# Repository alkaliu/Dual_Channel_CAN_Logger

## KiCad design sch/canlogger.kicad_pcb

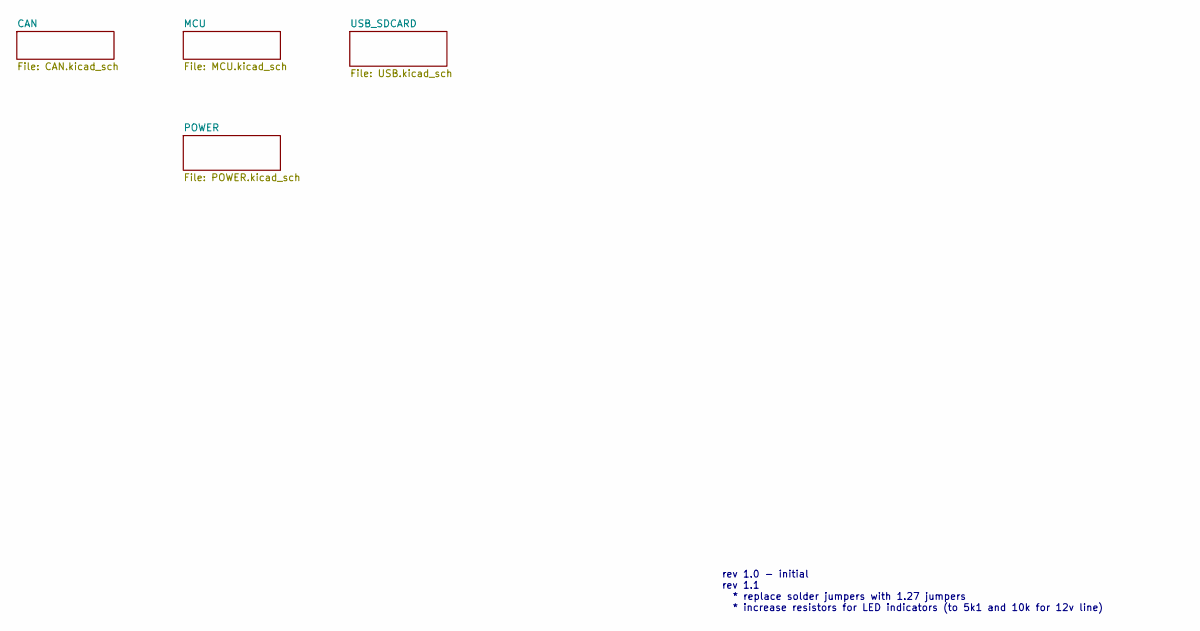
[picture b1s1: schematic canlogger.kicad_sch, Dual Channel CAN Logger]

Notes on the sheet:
rev 1.0 - initial rev 1.1 * replace solder jumpers with 1.27 jumpers * increase resistors for LED indicators (to 5k1 and 10k for 12v line)

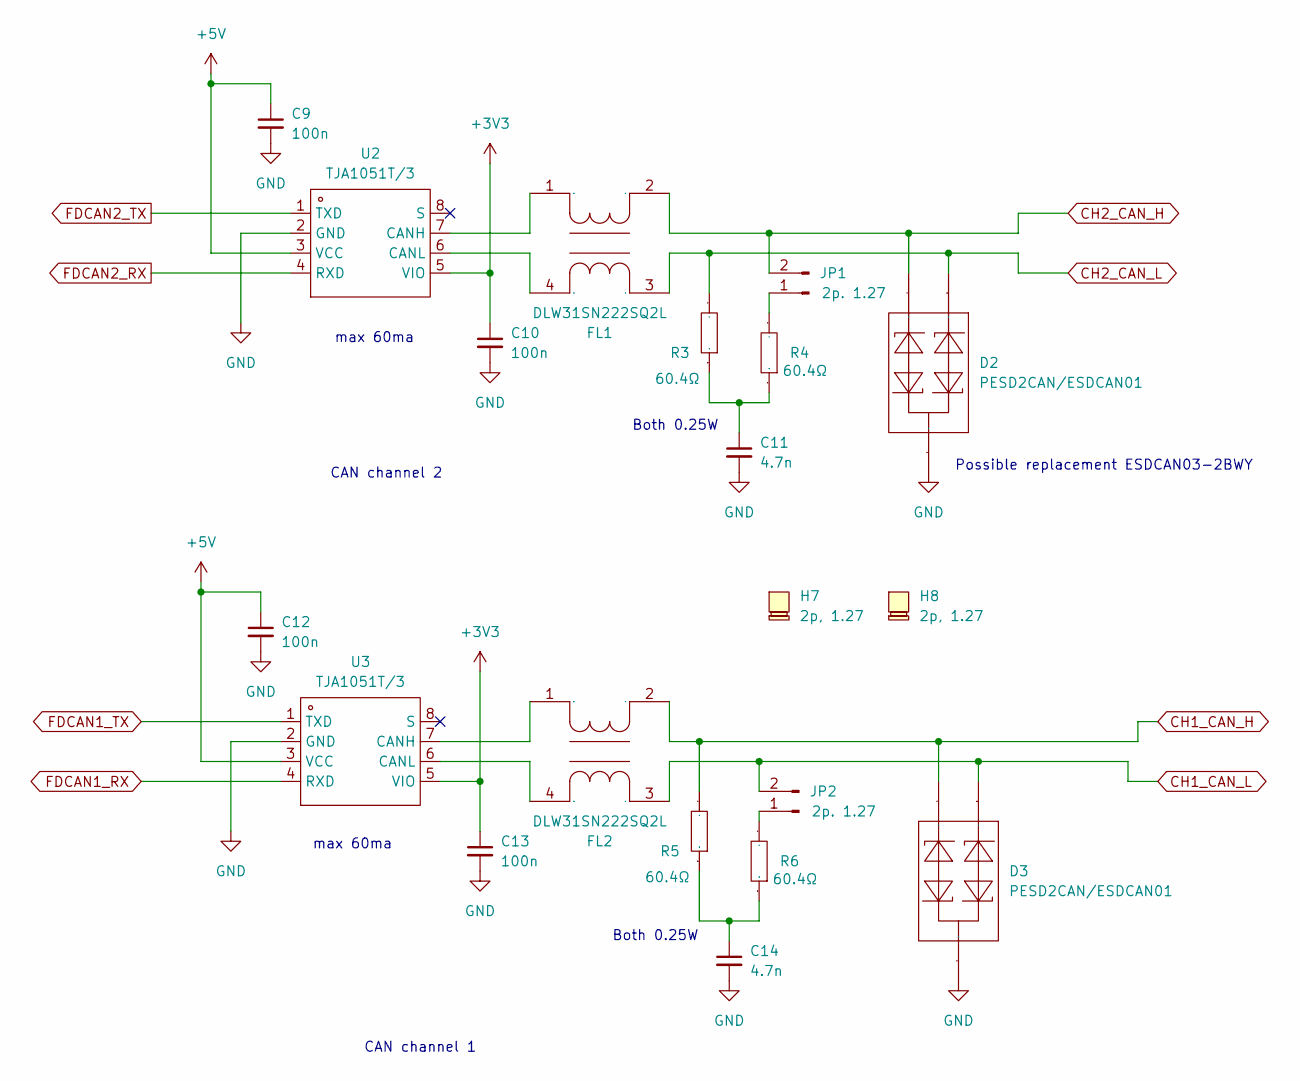
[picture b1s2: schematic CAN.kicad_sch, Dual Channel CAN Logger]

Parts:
C9, C10, C12, C13: 100n; C0603
C11, C14: 4.7n; C0603
D2, D3: PESD2CAN/ESDCAN01; SOT-23-3_L2.9-W1.3-P1.90-LS2.4-BR; Manufacturer Part PESD2CAN,215; LCSC Part Name 双向ESD 24V截止 峰值脉冲电流：5A@8/20us
FL1, FL2: DLW31SN222SQ2L; FILTER-SMD_4P-L3.2-W1.6-BL_DLW31SN222SQ2L; Manufacturer Part DLW31SN222SQ2L; LCSC Part Name 两路 贴片共模滤波器 阻抗2.2kΩ@100MHz
H7, H8: 2p, 1.27; LCSC Part Name C150949
JP1, JP2: 2p. 1.27; PinHeader_1x02_P1.27mm_Vertical
R3, R4, R5, R6: 60.4Ω; R1206; Manufacturer Part 1206W4F604JT5E; LCSC Part Name 60.4Ω ±1% 250mW 厚膜电阻
U2, U3: TJA1051T/3; SOIC-8_L4.9-W3.9-P1.27-LS6.0-BL; Manufacturer Part TJA1051T/3/1J; LCSC Part Name TJA1051T/3/1J

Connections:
+3V3: C10.1, C13.1, U2.5 (VIO), U3.5 (VIO); also elsewhere on the board
+5V: C9.1, C12.1, U2.3 (VCC), U3.3 (VCC); also elsewhere on the board
CH1_CAN_H: D3.2, FL2.2, R5.2; also elsewhere on the board
CH1_CAN_L: D3.1, FL2.3, JP2.2; also elsewhere on the board
CH2_CAN_H: D2.2, FL1.2, JP1.2; also elsewhere on the board
CH2_CAN_L: D2.1, FL1.3, R3.2; also elsewhere on the board
FDCAN1_RX: U3.4 (RXD); also elsewhere on the board
FDCAN1_TX: U3.1 (TXD); also elsewhere on the board
FDCAN2_RX: U2.4 (RXD); also elsewhere on the board
FDCAN2_TX: U2.1 (TXD); also elsewhere on the board
GND: C9.2, C10.2, C11.2, C12.2, C13.2, C14.2, D2.3, D3.3, U2.2 (GND), U3.2 (GND); also elsewhere on the board
unnamed: C11.1, R3.1, R4.1
unnamed: C14.1, R5.1, R6.1
unnamed: JP1.1, R4.2
unnamed: JP2.1, R6.2
unnamed: FL1.1, U2.7 (CANH)
unnamed: FL1.4, U2.6 (CANL)
unnamed: FL2.1, U3.7 (CANH)
unnamed: FL2.4, U3.6 (CANL)

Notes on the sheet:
Both 0.25W
max 60ma
CAN channel 2
Possible replacement ESDCAN03-2BWY
CAN channel 1

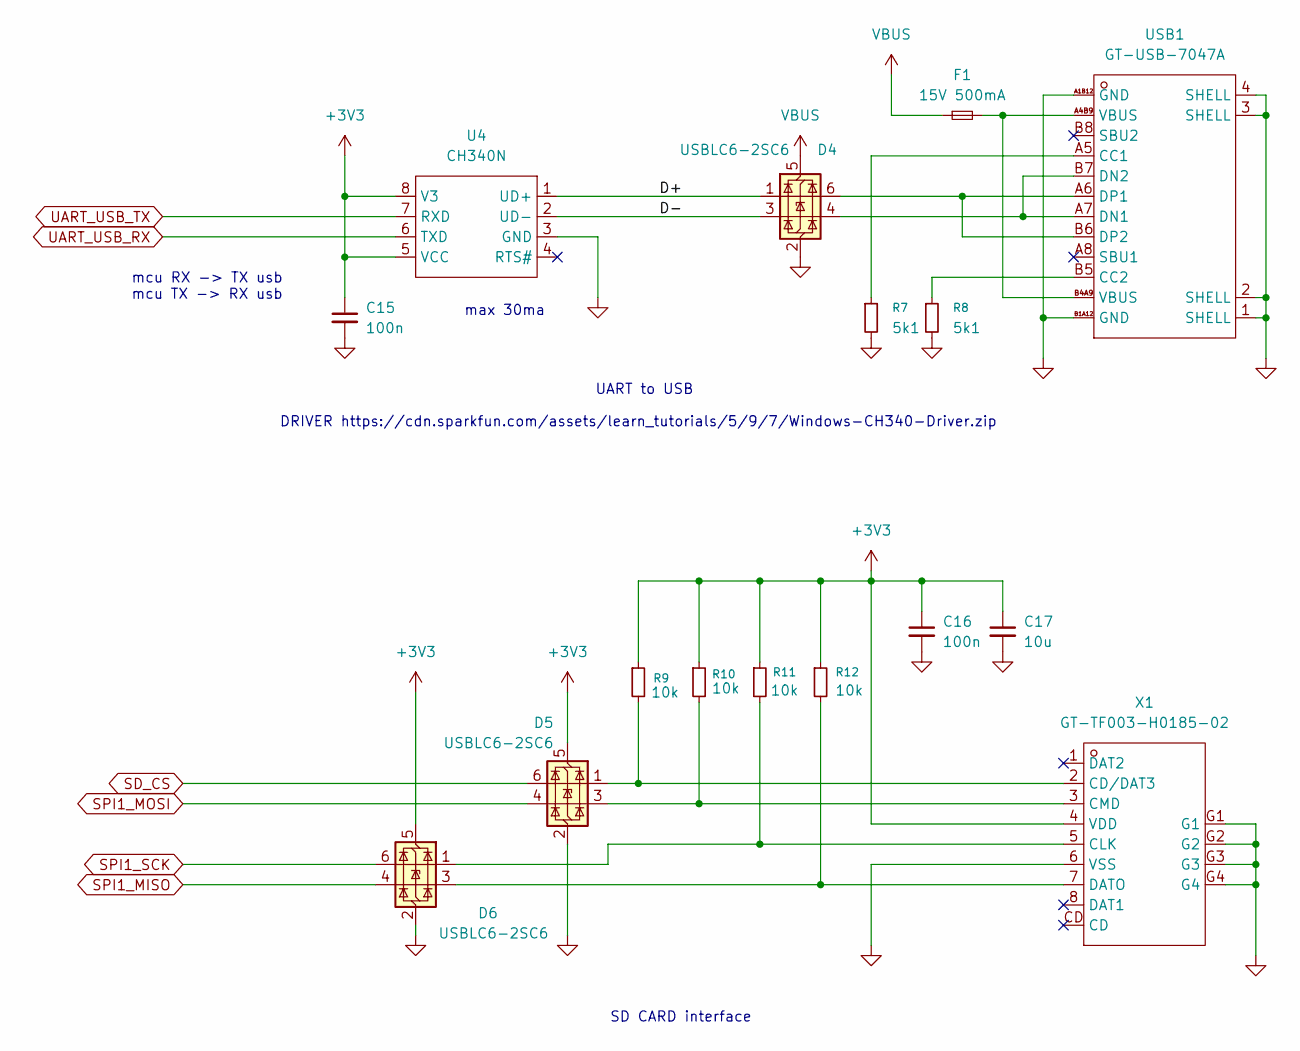
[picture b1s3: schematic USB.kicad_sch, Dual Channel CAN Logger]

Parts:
C15, C16: 100n; C0603
C17: 10u; C0805
D4, D5, D6: USBLC6-2SC6; SOT-23-6_L2.9-W1.6-P0.95-LS2.8-BL; Manufacturer Part USBLC6-2SC6; LCSC Part Name 单向ESD
F1: 15V 500mA; F1812; Manufacturer Part SMD1812P050TF; LCSC Part Name 15V 500mA 1812自恢复
R7, R8: 5k1; R0603
R9, R10, R11, R12: 10k; R0603
U4: CH340N; SOP-8_L4.9-W3.9-P1.27-LS6.0-BL; Manufacturer Part CH340N; LCSC Part Name USB2.0芯片CH340
USB1: GT-USB-7047A; USB-C-SMD_GT-USB-7047A; Manufacturer Part GT-USB-7047A; LCSC Part Name Type-C 母 卧贴
X1: GT-TF003-H0185-02; SIM-SMD_GT-TF003-H0185-02; Manufacturer Part GT-TF003-H0185-02; LCSC Part Name 自弹式 MicroSD卡(TF卡) 卡座

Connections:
+3V3: C15.1, C16.1, C17.1, D5.5 (VBUS), D6.5 (VBUS), R9.1, R10.1, R11.1, R12.1, U4.5 (VCC), U4.8 (V3), X1.4 (VDD); also elsewhere on the board
/USB_SDCARD/D+: D4.1 (I/O1), U4.1 (UD+)
/USB_SDCARD/D-: D4.3 (I/O2), U4.2 (UD-)
GND: C15.2, C16.2, C17.2, D4.2 (GND), D5.2 (GND), D6.2 (GND), R7.2, R8.2, U4.3 (GND), USB1.1 (SHELL), USB1.2 (SHELL), USB1.3 (SHELL), USB1.4 (SHELL), USB1.A1B12 (GND), USB1.B1A12 (GND), X1.6 (VSS), X1.G1, X1.G2, X1.G3, X1.G4; also elsewhere on the board
unnamed: F1.2, USB1.A4B9 (VBUS), USB1.B4A9 (VBUS)
unnamed: R7.1, USB1.A5 (CC1)
unnamed: R8.1, USB1.B5 (CC2)
unnamed: D4.4 (I/O2), USB1.A7 (DN1), USB1.B7 (DN2)
unnamed: D4.6 (I/O1), USB1.A6 (DP1), USB1.B6 (DP2)
unnamed: D5.1 (I/O1), R9.2, X1.2 (CD/DAT3)
unnamed: D6.1 (I/O1), R11.2, X1.5 (CLK)
unnamed: D5.3 (I/O2), R10.2, X1.3 (CMD)
unnamed: D6.3 (I/O2), R12.2, X1.7 (DATO)
SD_CS: D5.6 (I/O1); also elsewhere on the board
SPI1_MISO: D6.4 (I/O2); also elsewhere on the board
SPI1_MOSI: D5.4 (I/O2); also elsewhere on the board
SPI1_SCK: D6.6 (I/O1); also elsewhere on the board
UART_USB_RX: U4.6 (TXD); also elsewhere on the board
UART_USB_TX: U4.7 (RXD); also elsewhere on the board
VBUS: D4.5 (VBUS), F1.1; also elsewhere on the board

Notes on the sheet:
SD CARD interface
DRIVER https://cdn.sparkfun.com/assets/learn_tutorials/5/9/7/Windows-CH340-Driver.zip
max 30ma
mcu RX -> TX usb mcu TX -> RX usb
UART to USB

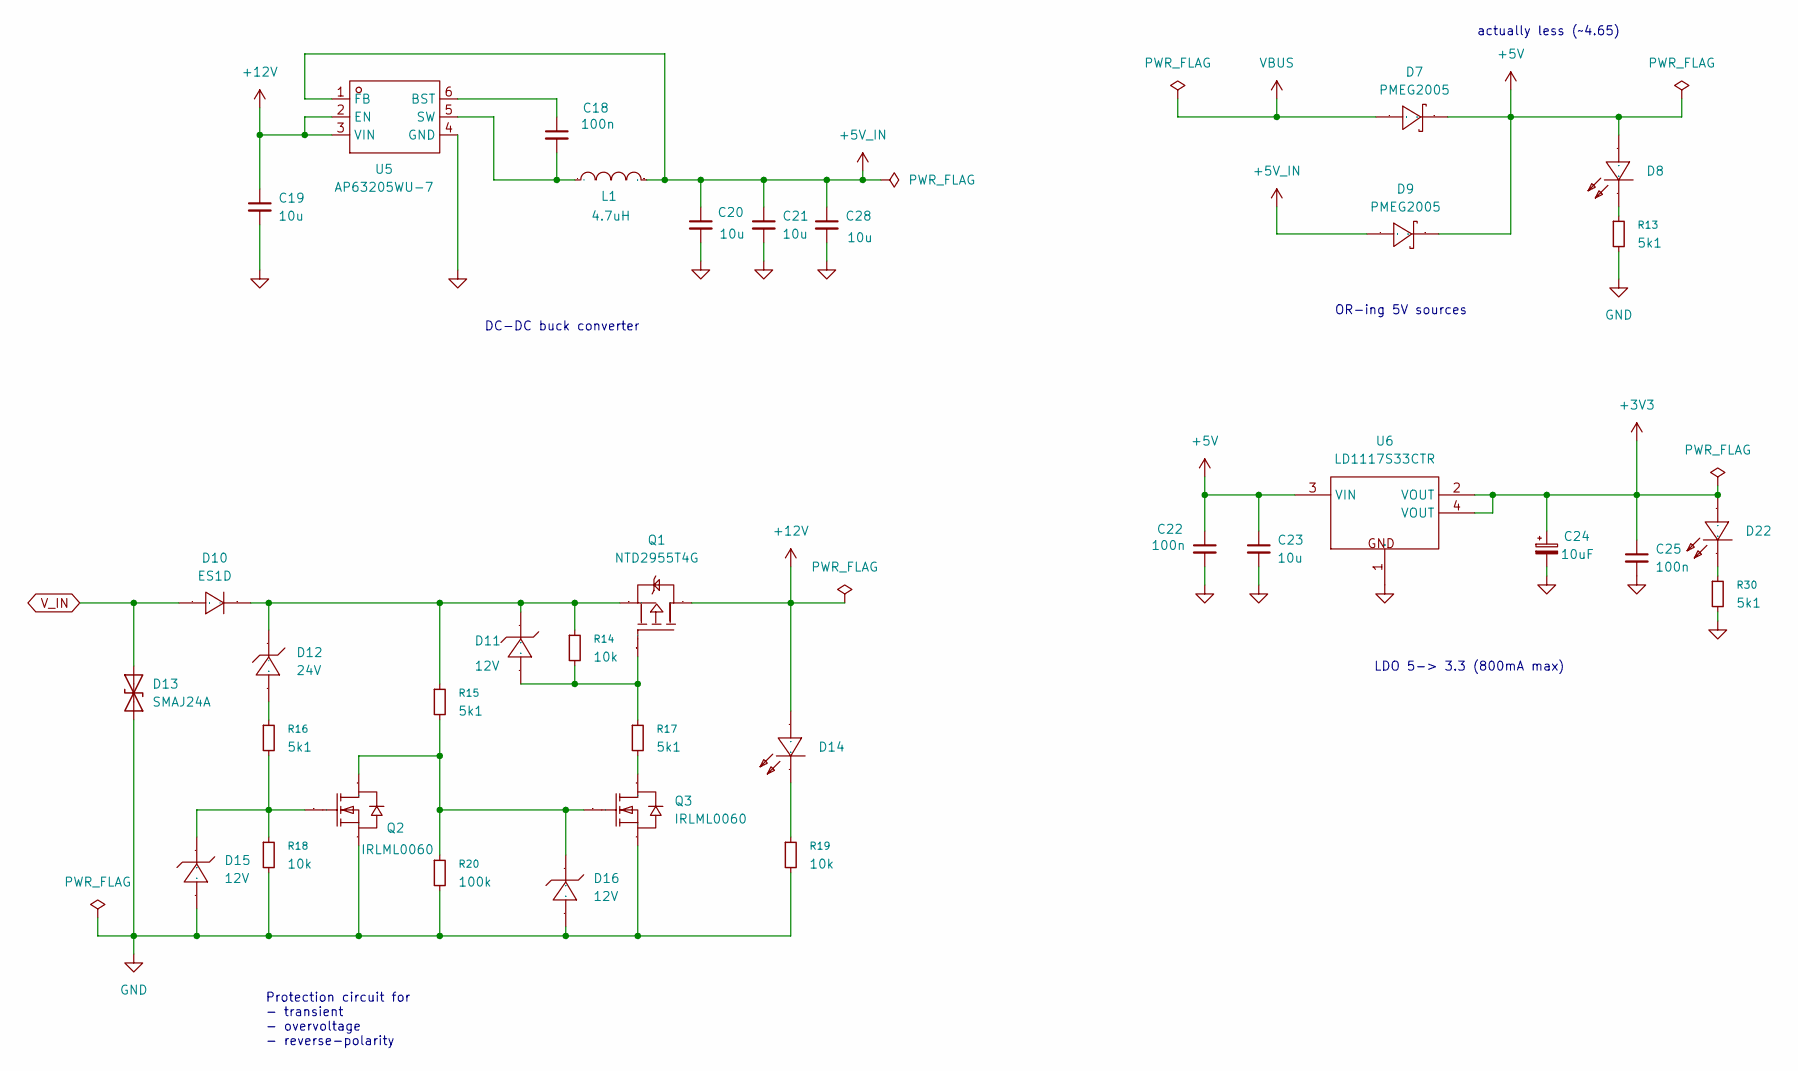
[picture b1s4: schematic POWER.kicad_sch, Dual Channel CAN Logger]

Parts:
C18, C22, C25: 100n; C0603
C19, C20, C21, C23, C28: 10u; C0805
C24: 10uF; CASE-A_3216; Manufacturer Part TAJA106K010RNJ; LCSC Part Name 10uF ±10% 10V
D7, D9: PMEG2005; SOD-123_L2.8-W1.8-LS3.7-RD; Manufacturer Part PMEG2005EGWX; LCSC Part Name 电压:20V 电流:500mA
D8, D14, D22: LED0603-RD; Manufacturer Part KT-0603R; LCSC Part Name 0603 红灯 高亮
D10: ES1D; SMA_L4.3-W2.6-LS5.2-RD; Manufacturer Part ES1D-E3/61T; LCSC Part Name 耐压:200V 电流:1A 反向恢复时间：15ns
D11, D15, D16: 12V; SOD-123_L2.8-W1.8-LS3.7-RD; Manufacturer Part MMSZ12T1G; LCSC Part Name MMSZ12T1G
D12: 24V; SOD-123_L2.8-W1.8-LS3.7-RD; Manufacturer Part MMSZ5252BT1G; LCSC Part Name MMSZ5252BT1G
D13: SMAJ24A; SMA_L4.4-W2.6-LS5.0-RD; Manufacturer Part SMAJ24A; LCSC Part Name 单向TVS 24V截止 10.3A峰值脉冲
L1: 4.7uH; IND-SMD_L4.4-W4.2-A; Manufacturer Part 0420CDMCCDS-4R7MC; LCSC Part Name 4.7uH ±20% 3A
Q1: NTD2955T4G; TO-252-2_L6.6-W6.1-P4.57-LS9.9-TL-CW; Manufacturer Part NTD2955T4G; LCSC Part Name 1个P沟道 耐压:60V 电流:12A
Q2, Q3: IRLML0060; SOT-23-3_L2.9-W1.6-P1.90-LS2.8-BR; Manufacturer Part IRLML0060TRPBF; LCSC Part Name 1个N沟道 耐压:60V 电流:2.7A
R13, R15, R16, R17, R30: 5k1; R0603
R14, R18, R19: 10k; R0603
R20: 100k; R0603
U5: AP63205WU-7; TSOT-23-6_L2.9-W1.6-P0.95-LS2.8-BL; Manufacturer Part AP63205WU-7; LCSC Part Name 3.8V至32V输入、2A低静态电流同步降压转换器，增强EMI抑制
U6: LD1117S33CTR; SOT-223-4_L6.5-W3.5-P2.30-LS7.0-BR; Manufacturer Part LD1117S33CTR; LCSC Part Name 可调与固定低压降正电压稳压器

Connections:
+3V3: C24.1, C25.1, D22.2 (A), U6.2 (VOUT), U6.4 (VOUT); also elsewhere on the board
+5V: C22.1, C23.1, D7.1 (A), D8.2 (A), D9.1 (A), U6.3 (VIN); also elsewhere on the board
+5V_IN: C20.1, C21.1, C28.1, D9.2 (K), L1.1, U5.1 (FB)
+12V: C19.1, D14.2 (A), Q1.2 (D), U5.2 (EN), U5.3 (VIN)
GND: C19.2, C20.2, C21.2, C22.2, C23.2, C24.2, C25.2, C28.2, D13.2 (A2), D15.2 (A), D16.2 (A), Q2.2 (S), Q3.2 (S), R13.2, R18.2, R19.2, R20.2, R30.2, U5.4 (GND), U6.1 (GND); also elsewhere on the board
unnamed: D8.1 (K), R13.1
unnamed: D10.1 (C), D11.1 (K), D12.1 (C), Q1.3 (S), R14.1, R15.1
unnamed: D11.2 (A), Q1.1 (G), R14.2, R17.1
unnamed: D12.2 (A), R16.1
unnamed: D14.1 (K), R19.1
unnamed: D15.1 (K), Q2.1 (G), R16.2, R18.1
unnamed: D16.1 (K), Q2.3 (D), Q3.1 (G), R15.2, R20.1
unnamed: D22.1 (K), R30.1
unnamed: Q3.3 (D), R17.2
unnamed: C18.1, U5.6 (BST)
unnamed: C18.2, L1.2, U5.5 (SW)
VBUS: D7.2 (K); also elsewhere on the board
V_IN: D10.2 (A), D13.1 (A1); also elsewhere on the board

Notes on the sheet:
LDO 5-> 3.3 (800mA max)
OR-ing 5V sources
DC-DC buck converter
actually less (~4.65)
Protection circuit for - transient - overvoltage - reverse-polarity

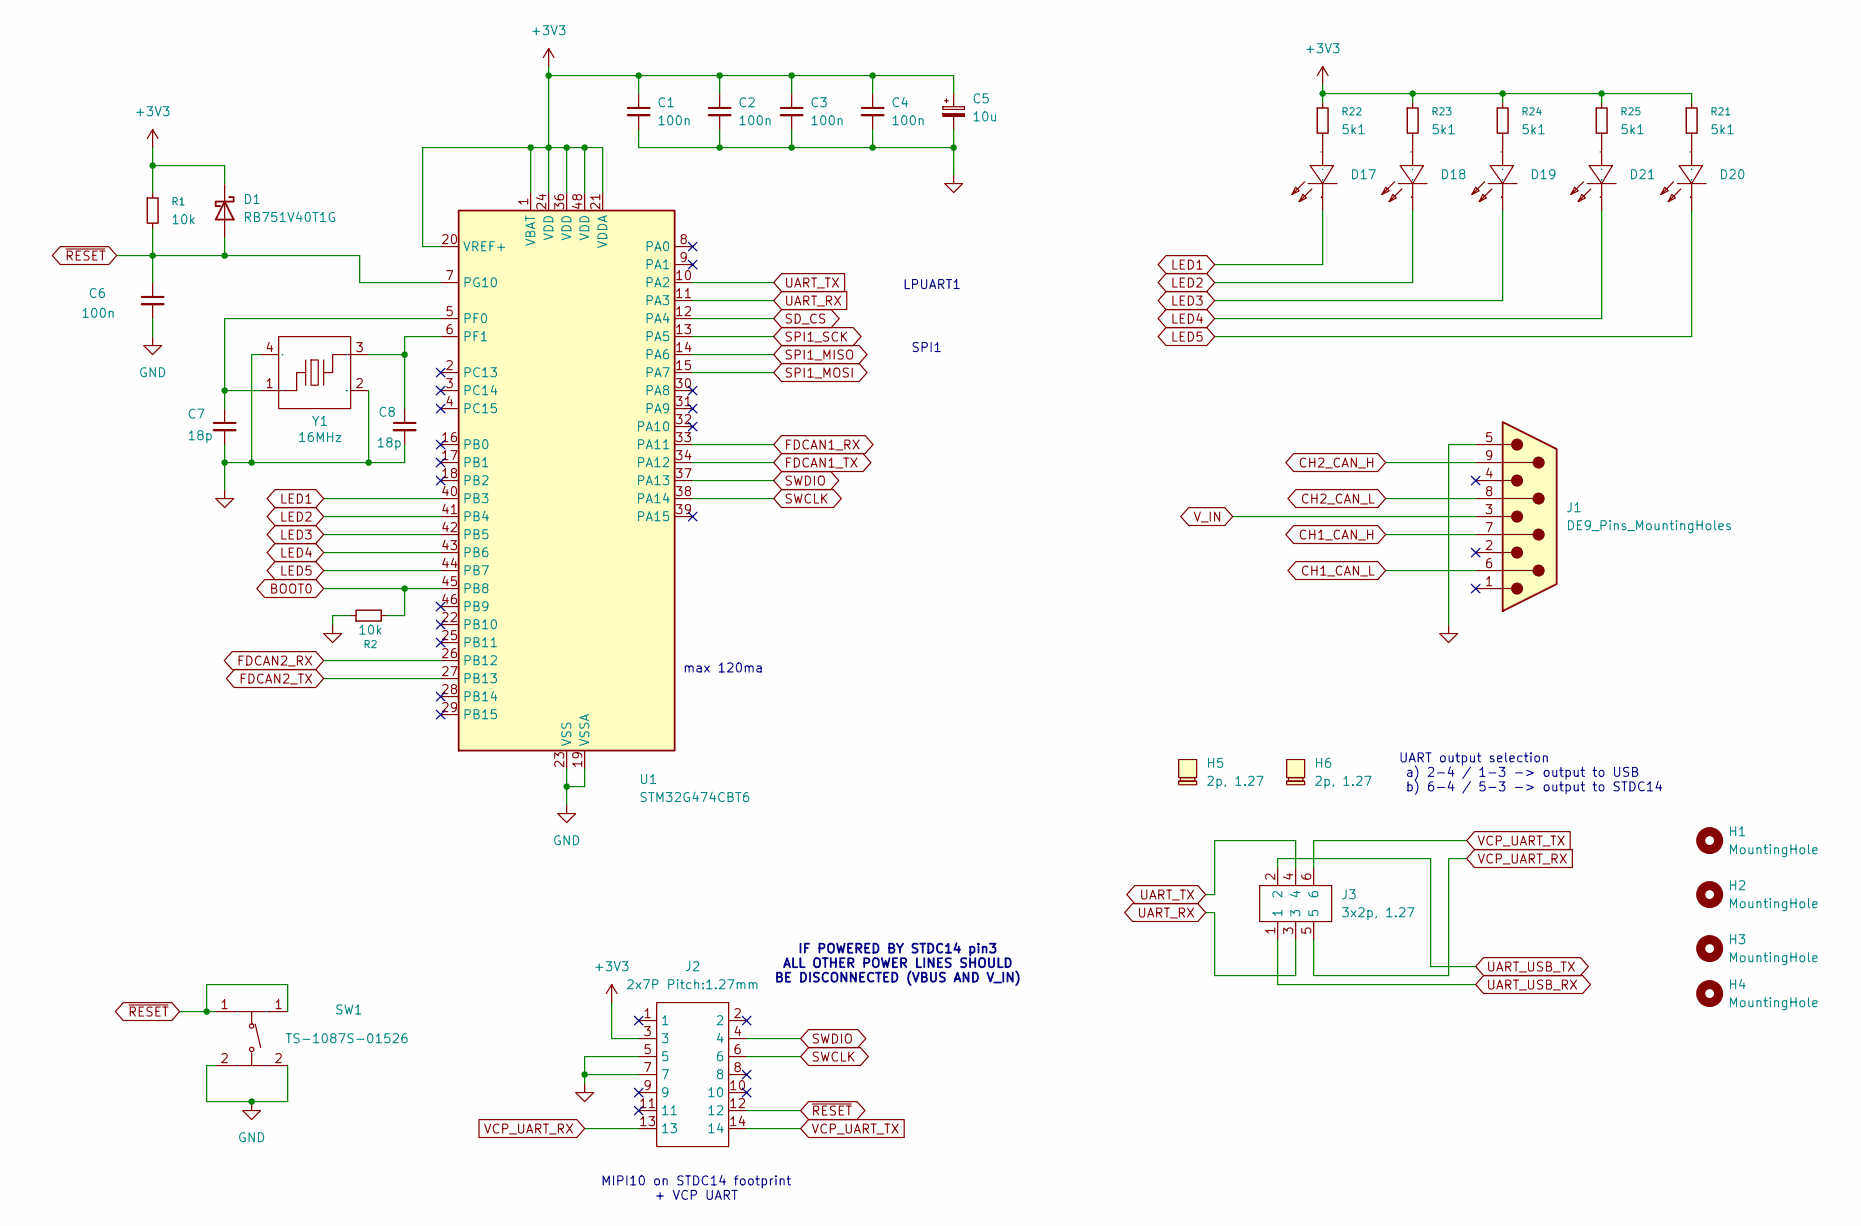
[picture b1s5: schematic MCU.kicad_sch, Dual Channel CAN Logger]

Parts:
C1, C2, C3, C4, C6: 100n; C0603
C5: 10u; C0805
C7, C8: 18p; C0603
D1: RB751V40T1G; SOD-323_L1.8-W1.3-LS2.5-RD; Manufacturer Part RB751V40T1G; LCSC Part Name 电压:30V 电流:30mA
D17, D18, D19, D20, D21: LED0603-RD; Manufacturer Part KT-0603R; LCSC Part Name 0603 红灯 高亮
H1, H2, H3, H4: MountingHole; MountingHole_2.7mm_M2.5_Pad_TopBottom
H5, H6: 2p, 1.27; LCSC Part Name C150949
J1: DE9_Pins_MountingHoles; DSUB-9_Pins_EdgeMount_P2.77mm
J2: 2x7P Pitch:1.27mm; HDR-SMD_14P-P1.27_HX-PZ1.27-2X7P-TP; Manufacturer Part HX PZ1.27-2x7P TP; LCSC Part Name 2x7P 间距:1.27mm 方针 立贴
J3: 3x2p, 1.27; HDR-SMD_6P-P1.27-V-M-R2-C3-S1.27-LS5.5-1; Manufacturer Part DZ127S-22-06-55; LCSC Part Name 2x3P 间距:1.27mm 方针 立贴
R1, R2: 10k; R0603
R21, R22, R23, R24, R25: 5k1; R0603
SW1: TS-1087S-01526; SW-SMD_L5.2-W5.2-P3.70-LS6.4; Manufacturer Part TS-1087S-01526; LCSC Part Name 5.2*5.2*1.5mm 立贴 轻触开关
U1: STM32G474CBT6; LQFP-48_L7.0-W7.0-P0.50-LS9.0-BL; Manufacturer Part STM32G474CBT6; LCSC Part Name STM32G474CBT6
Y1: 16MHz; CRYSTAL-SMD_4P-L3.2-W2.5-BL_SIT8008BI; Manufacturer Part CF4016M00009001; LCSC Part Name 16MHz ±10ppm 9pF

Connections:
+3V3: C1.1, C2.1, C3.1, C4.1, C5.1, D1.1 (K), J2.3, R1.1, R21.1, R22.1, R23.1, R24.1, R25.1, U1.1 (VBAT), U1.20 (VREF+), U1.21 (VDDA), U1.24 (VDD), U1.36 (VDD), U1.48 (VDD); also elsewhere on the board
BOOT0: R2.2, U1.45 (PB8)
CH1_CAN_H: J1.7; also elsewhere on the board
CH1_CAN_L: J1.6; also elsewhere on the board
CH2_CAN_H: J1.9; also elsewhere on the board
CH2_CAN_L: J1.8; also elsewhere on the board
FDCAN1_RX: U1.33 (PA11); also elsewhere on the board
FDCAN1_TX: U1.34 (PA12); also elsewhere on the board
FDCAN2_RX: U1.26 (PB12); also elsewhere on the board
FDCAN2_TX: U1.27 (PB13); also elsewhere on the board
GND: C1.2, C2.2, C3.2, C4.2, C5.2, C6.2, C7.2, C8.2, J1.5, J2.5, J2.7, R2.1, SW1.2, U1.19 (VSSA), U1.23 (VSS), U1.35 (VSS), U1.47 (VSS), Y1.2 (GND), Y1.4 (GND); also elsewhere on the board
LED1: D17.1 (K), U1.40 (PB3)
LED2: D18.1 (K), U1.41 (PB4)
LED3: D19.1 (K), U1.42 (PB5)
LED4: D21.1 (K), U1.43 (PB6)
LED5: D20.1 (K), U1.44 (PB7)
unnamed: D17.2 (A), R22.2
unnamed: D18.2 (A), R23.2
unnamed: D19.2 (A), R24.2
unnamed: D20.2 (A), R21.2
unnamed: D21.2 (A), R25.2
unnamed: C7.1, U1.5 (PF0), Y1.1
unnamed: C8.1, U1.6 (PF1), Y1.3
SD_CS: U1.12 (PA4); also elsewhere on the board
SPI1_MISO: U1.14 (PA6); also elsewhere on the board
SPI1_MOSI: U1.15 (PA7); also elsewhere on the board
SPI1_SCK: U1.13 (PA5); also elsewhere on the board
SWCLK: J2.6, U1.38 (PA14)
SWDIO: J2.4, U1.37 (PA13)
UART_RX: J3.3, U1.11 (PA3)
UART_TX: J3.4, U1.10 (PA2)
UART_USB_RX: J3.1; also elsewhere on the board
UART_USB_TX: J3.2; also elsewhere on the board
VCP_UART_RX: J2.13, J3.5
VCP_UART_TX: J2.14, J3.6
V_IN: J1.3; also elsewhere on the board
~RESET: C6.1, D1.2 (A), J2.12, R1.2, SW1.1, U1.7 (PG10)

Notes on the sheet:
MIPI10 on STDC14 footprint + VCP UART
UART output selection a) 2-4 / 1-3 -> output to USB b) 6-4 / 5-3 -> output to STDC14
LPUART1
max 120ma
SPI1
IF POWERED BY STDC14 pin3 ALL OTHER POWER LINES SHOULD BE DISCONNECTED (VBUS AND V_IN)

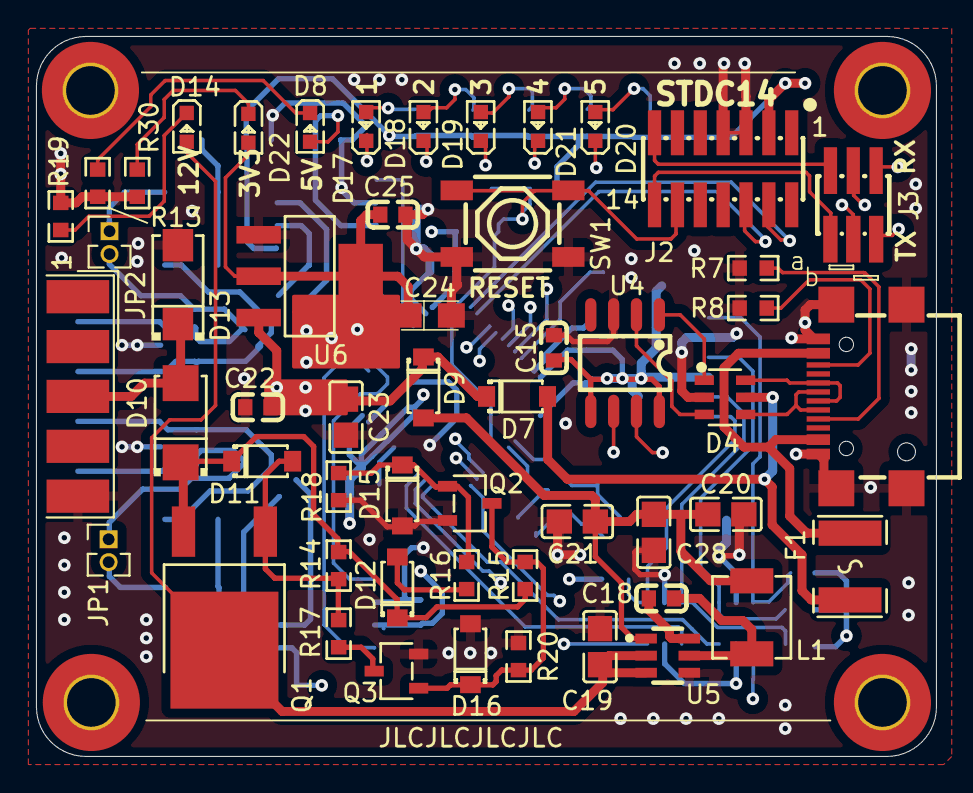
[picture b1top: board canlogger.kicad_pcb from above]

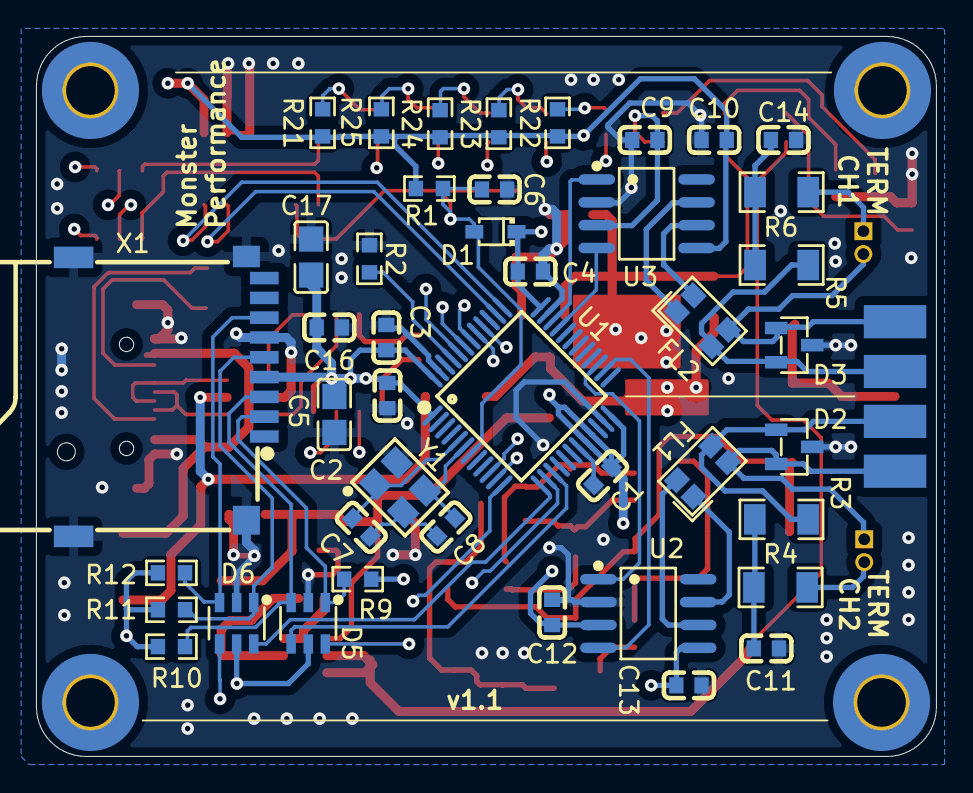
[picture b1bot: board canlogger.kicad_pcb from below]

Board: 4 copper layers, 50.0 x 40.0 mm, 100 parts (43 on the bottom side), 71 nets.

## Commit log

2025-11-24 v1.1 changes * increase LED resistors as they are too bright * replace solder jumpers with pins * add corresponding 3D models
2025-11-24 Preliminary shematic update for v1.1
